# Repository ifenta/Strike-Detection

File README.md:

# Strike-Detection
Ideally I want to be able to:
- correct different strike and block techniques
- calculate speed of the strikes
- count how many times you do different strikes (flow hitting on a heavy bag for example)

With the camera, I want: 
- correct form now that I can see the whole body and depth
- detect if you are doing a lead or rear punch/kick
- see if I can improve transitions from different techniques

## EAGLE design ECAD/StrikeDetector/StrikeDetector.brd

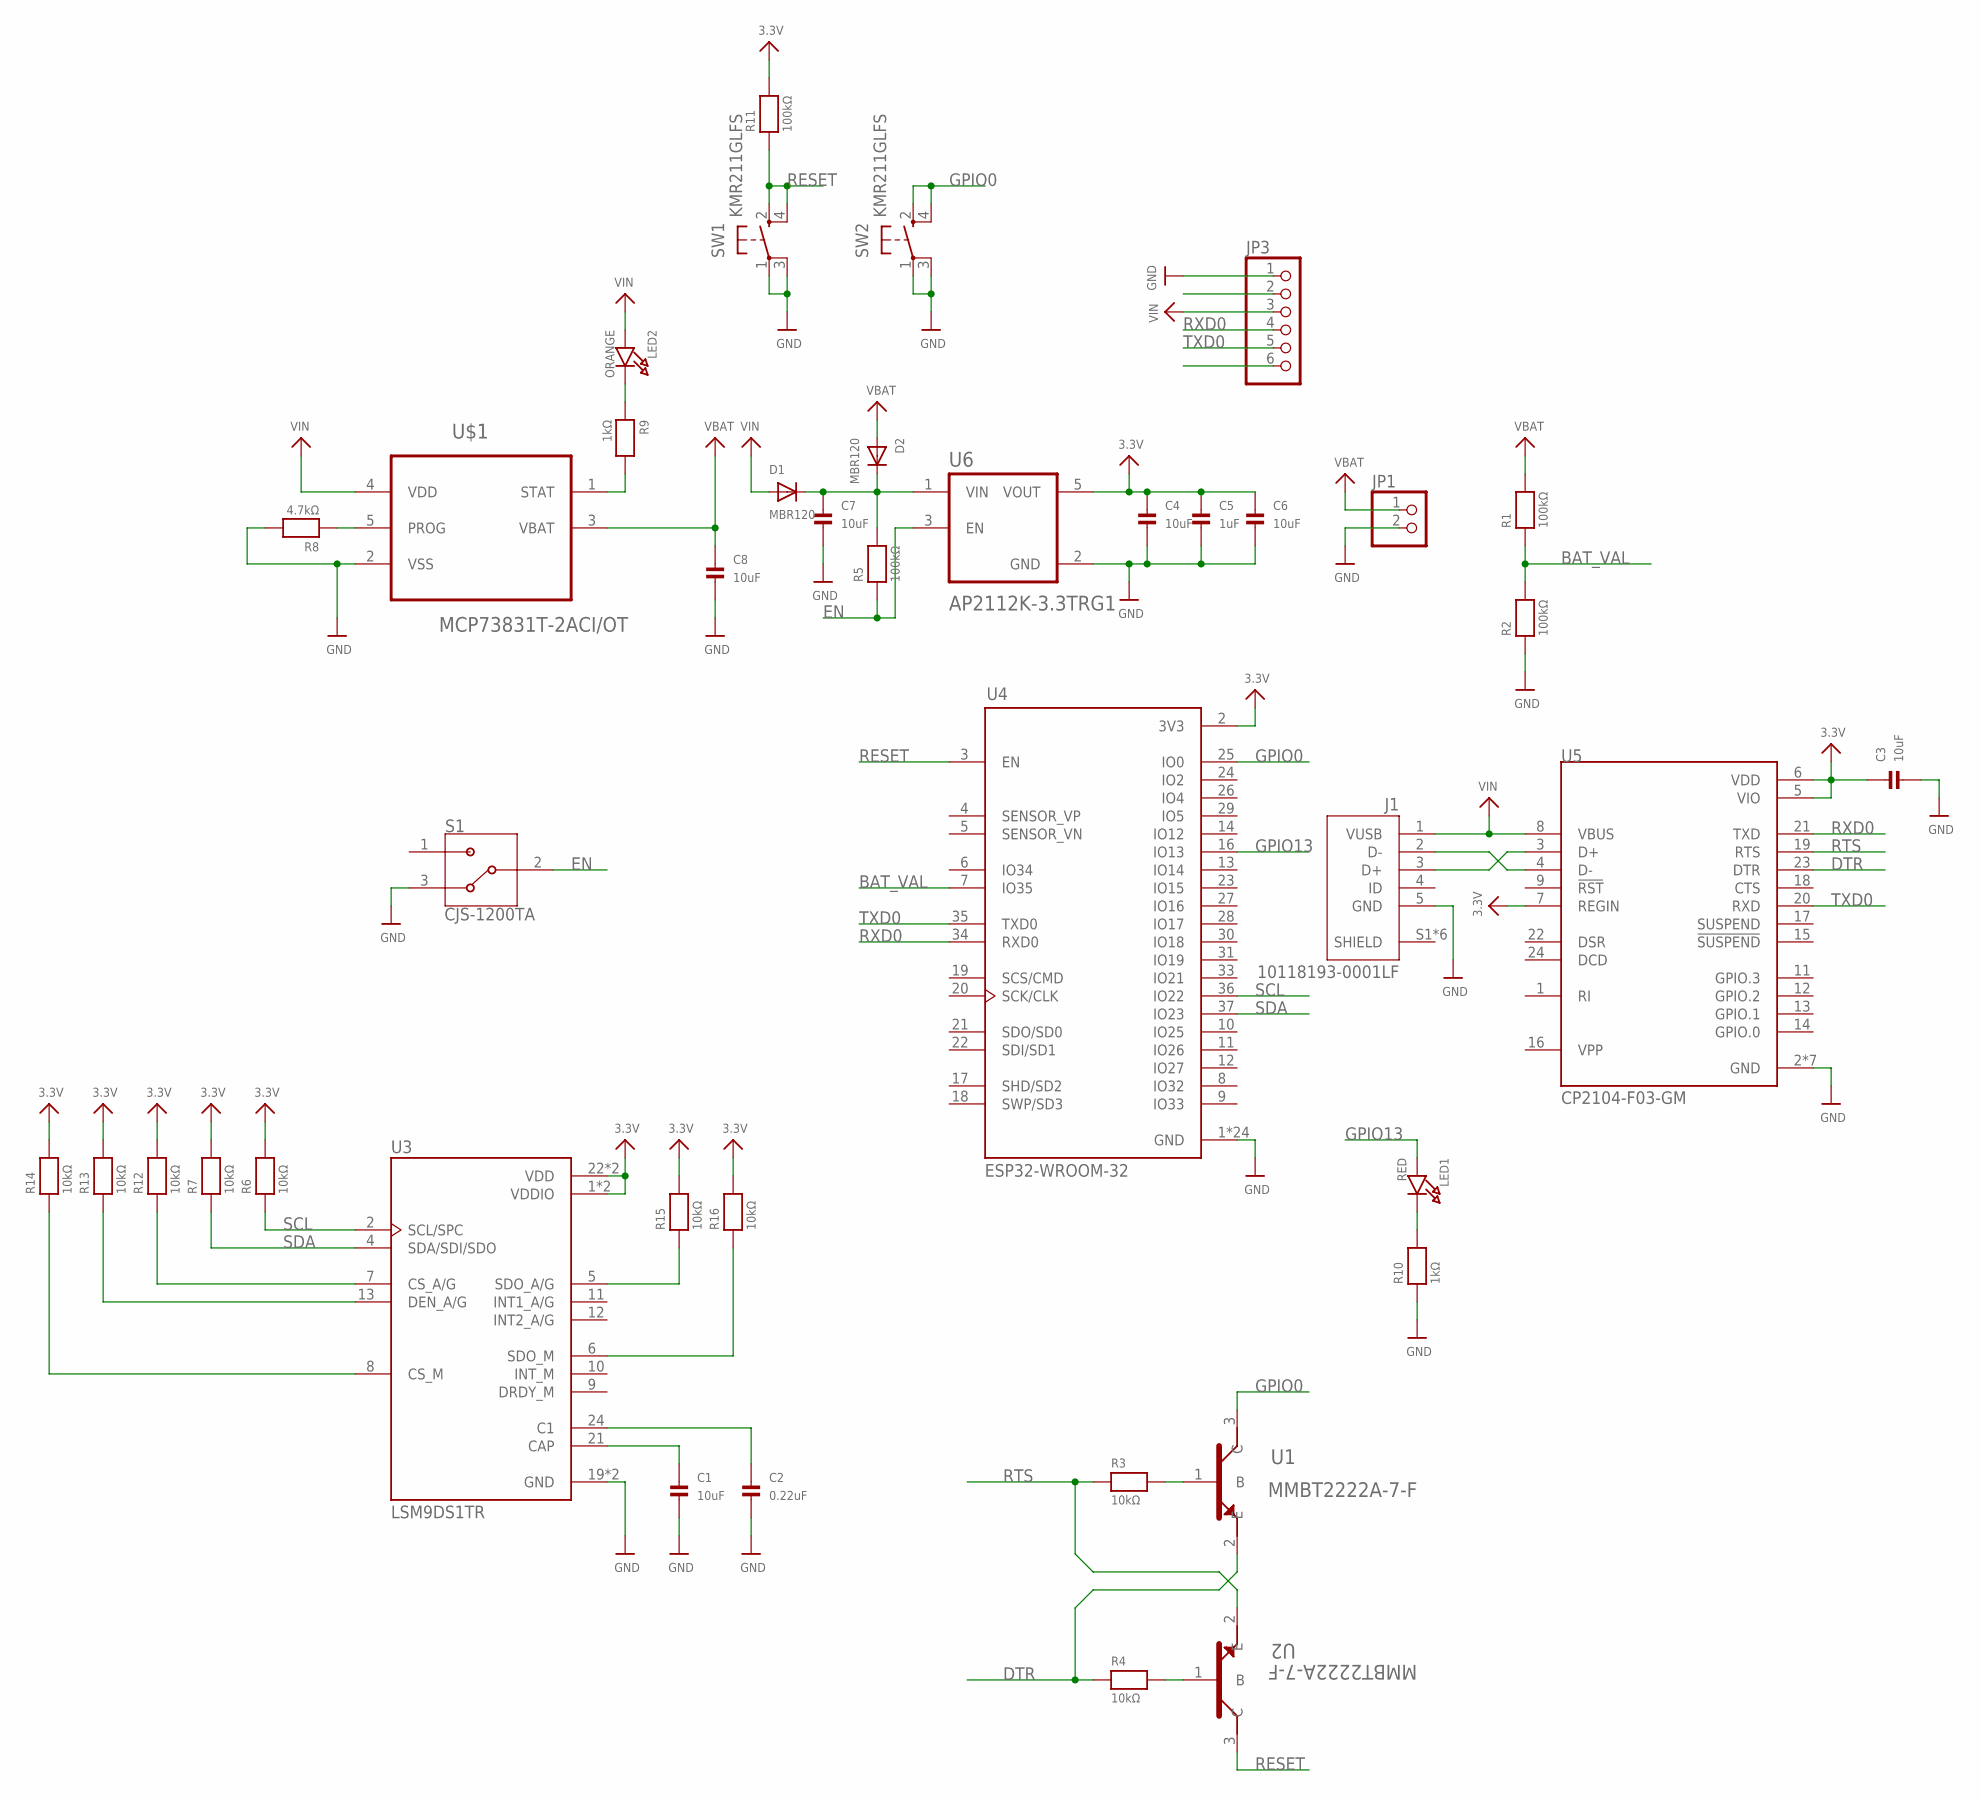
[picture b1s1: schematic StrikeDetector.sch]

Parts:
C1, C3, C4, C6, C7, C8: 10uF; 0603
C2: 0.22uF; 0603
C5: 1uF; 0603
D1, D2: MBR120; SOD-123
J1: 10118193-0001LF; FCI_10118193-0001LF
JP1: HEADER-1X2ROUND; 1X02_ROUND
JP3: HEADER-1X6ROUND; 1X06_ROUND
LED1: RED; CHIPLED_0603
LED2: ORANGE; CHIPLED_0603
R1, R2, R5, R11: 100kΩ; 0603
R3, R4, R6, R7, R12, R13, R14, R15, R16: 10kΩ; 0603
R8: 4.7kΩ; 0603
R9, R10: 1kΩ; 0603
S1: CJS-1200TA; SW_CJS-1200TA
SW1, SW2: KMR211GLFS; KMR2
U1, U2: MMBT2222A-7-F; SOT103P240X110-3N
U3: LSM9DS1TR; PQFN43P300X350X102-24N
U4: ESP32-WROOM-32; MODULE_ESP32-WROOM-32
U5: CP2104-F03-GM; QFN50P400X400X80-25N
U6: AP2112K-3.3TRG1; SOT95P285X140-5N
U$1: MCP73831T-2ACI/OT; SOT95P280X145-5N

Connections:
3.3V: C3.1, C4.1, C5.1, C6.1, R6.2, R7.2, R11.2, R12.2, R13.2, R14.2, R15.2, R16.2, U3.1 (VDDIO), U3.3 (VDDIO), U3.22 (VDD), U3.23 (VDD), U4.2 (3V3), U5.5 (VIO), U5.6 (VDD), U5.7 (REGIN), U6.5 (VOUT)
BAT_VAL: R1.1, R2.2, U4.7 (IO35)
DTR: R4.1, U1.2 (E), U5.23 (DTR)
EN: R5.1, S1.2, U6.3 (EN)
GND: C1.2, C2.2, C3.2, C4.2, C5.2, C6.2, C7.2, C8.2, J1.5 (GND), JP1.2, JP3.1, R2.1, R8.2, R10.1, S1.3, SW1.1, SW1.3 (P1), SW2.1, SW2.3 (P1), U3.19 (GND), U3.20 (GND), U4.1 (GND), U4.15 (GND), U4.38 (GND), U4.39_1 (GND), U4.39_2 (GND), U4.39_3 (GND), U4.39_4 (GND), U4.39_5 (GND), U4.39_6 (GND), U4.39_7 (GND), U4.39_8 (GND), U4.39_9 (GND), U4.39_10 (GND), U4.39_11 (GND), U4.39_12 (GND), U4.39_13 (GND), U4.39_14 (GND), U4.39_15 (GND), U4.39_16 (GND), U4.39_17 (GND), U4.39_18 (GND), U4.39_19 (GND), U4.39_20 (GND), U4.39_21 (GND), U5.2 (GND), U5.25 (GND), U5.THERM_1 (GND), U5.THERM_2 (GND), U5.THERM_3 (GND), U5.THERM_4 (GND), U5.THERM_5 (GND), U6.2 (GND), U$1.2 (VSS)
GPIO0: SW2.2 (S), SW2.4 (S1), U1.3 (C), U4.25 (IO0)
GPIO13: LED1.A, U4.16 (IO13)
unnamed: C1.1, U3.21 (CAP)
unnamed: J1.3 (D+), U5.3 (D+)
unnamed: J1.2 (D-), U5.4 (D-)
unnamed: C2.1, U3.24 (C1)
unnamed: R3.2, U1.1 (B)
unnamed: R4.2, U2.1 (B)
unnamed: C7.1, D1.C, D2.C, R5.2, U6.1 (VIN)
unnamed: R8.1, U$1.5 (PROG)
unnamed: R9.2, U$1.1 (STAT)
unnamed: LED2.C, R9.1
unnamed: LED1.C, R10.2
unnamed: R12.1, U3.7 (CS_A/G)
unnamed: R13.1, U3.13 (DEN_A/G)
unnamed: R14.1, U3.8 (CS_M)
unnamed: R15.1, U3.5 (SDO_A/G)
unnamed: R16.1, U3.6 (SDO_M)
RESET: R11.1, SW1.2 (S), SW1.4 (S1), U2.3 (C), U4.3 (EN)
RTS: R3.1, U2.2 (E), U5.19 (RTS)
RXD0: JP3.4, U4.34 (RXD0), U5.21 (TXD)
SCL: R6.1, U3.2 (SCL/SPC), U4.36 (IO22)
SDA: R7.1, U3.4 (SDA/SDI/SDO), U4.37 (IO23)
TXD0: JP3.5, U4.35 (TXD0), U5.20 (RXD)
VBAT: C8.1, D2.A, JP1.1, R1.2, U$1.3 (VBAT)
VIN: D1.A, J1.1 (VUSB), JP3.3, LED2.A, U5.8 (VBUS), U$1.4 (VDD)

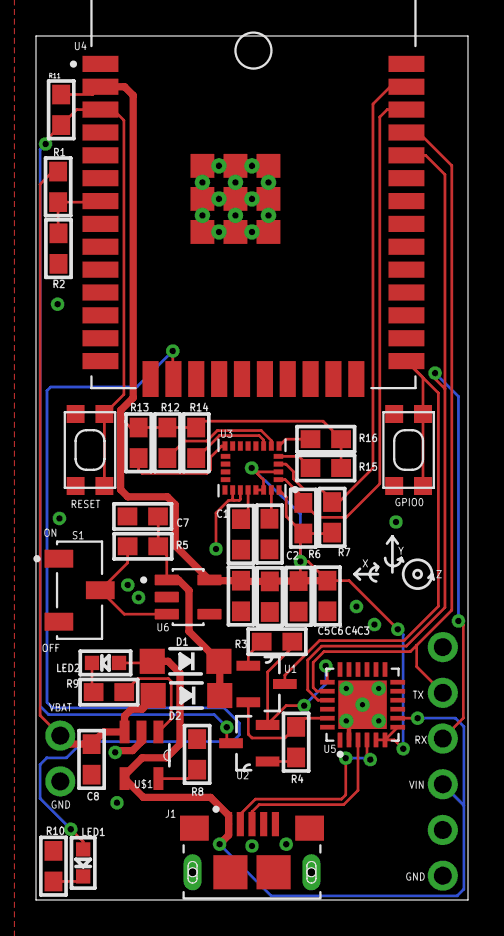
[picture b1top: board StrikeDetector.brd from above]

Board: 2 copper layers, 24.0 x 48.0 mm, 41 parts (0 on the bottom side), 31 nets.

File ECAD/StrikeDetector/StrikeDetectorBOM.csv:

"Qty";"Value";"Device";"Package";"Parts";"Description";"";
"1";"";"CP2104-F03-GM";"QFN50P400X400X80-25N";"U5";"USB-to-UART 1-CH 576byte FIFO 3.3V 24-Pin QFN EP T/R";"";
"1";"";"HEADER-1X2ROUND";"1X02_ROUND";"JP1";"PIN HEADER";"";
"1";"";"HEADER-1X6ROUND";"1X06_ROUND";"JP3";"PIN HEADER";"";
"1";"0.22uF";"CAP_CERAMIC0603";"0603";"C2";"Ceramic Capacitors";"";
"4";"100kΩ";"RESISTOR0603";"0603";"R1, R2, R5, R11";"Resistors";"";
"1";"10118193-0001LF";"10118193-0001LF";"FCI_10118193-0001LF";"J1";"Micro USB B Type Receptacle";"";
"2";"10kΩ";"RESISTOR0603";"0603";"R3, R4";"Resistors";"";
"6";"10uF";"CAP_CERAMIC0603";"0603";"C1, C3, C4, C6, C7, C8";"Ceramic Capacitors";"";
"2";"1kΩ";"RESISTOR0603";"0603";"R9, R10";"Resistors";"";
"1";"1uF";"CAP_CERAMIC0603";"0603";"C5";"Ceramic Capacitors";"";
"3";"4.7kΩ";"RESISTOR0603";"0603";"R6, R7, R8";"Resistors";"";
"1";"AP2112K-3.3TRG1";"AP2112K-3.3TRG1";"SOT95P285X140-5N";"U6";"AP2112 Series 0.6 A 3.3 V Fixed Output SMT LDO Linear Regulator - SOT23-5";"";
"1";"CJS-1200TA";"CJS-1200TA";"SW_CJS-1200TA";"S1";"Switch Slide N.O./N.C. SPDT Raised Slide 0.1A 24VDC J-Hook SMD Embossed T/R";"";
"1";"ESP32-WROOM-32";"ESP32-WROOM-32";"MODULE_ESP32-WROOM-32";"U4";"Bluetooth, WiFi Transceiver Module 2.4GHz ~ 2.5GHz Surface Mount";"";
"2";"KMR211GLFS";"SPST_TACT-KMR2";"KMR2";"SW1, SW2";"SMT 6mm switch, EVQQ2 series";"";
"1";"LSM9DS1TR";"LSM9DS1TR";"PQFN43P300X350X102-24N";"U3";"The LSM9DS1 is a system-in-package featuring a";"";
"2";"MBR120";"DIODESOD-123";"SOD-123";"D1, D2";"Diode";"";
"1";"MCP73831T-2ACI/OT";"MCP73831T-2ACI/OT";"SOT95P280X145-5N";"U$1";"Charge Management Controller";"";
"2";"MMBT2222A-7-F";"MMBT2222A-7-F";"SOT103P240X110-3N";"U1, U2";"NPN SMALL SIGNAL SURFACE MOUNT TRANSISTOR";"";
"1";"ORANGE";"LED0603";"CHIPLED_0603";"LED2";"LED";"";
"1";"RED";"LED0603";"CHIPLED_0603";"LED1";"LED";"";

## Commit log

2019-07-26 init commit
2020-02-17 Organizing
    Tranfering Arduino code to PlatformIO
    Organizing folders
2020-02-17 Clean up .ino file
2020-02-18 Sending Data Over Wifi
    Did a bit of organizing of files
    Able to send IMU data over UDP to my computer and run the python script to determine what kind of punch it is. Need to work a bit more on the analysis and how to incorporate it together with the rest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
2020-02-26 Created src
    Combine colletion of data over udp, read data, find the different strikes and plot data in one script. All in src folder
2020-02-26 Adding comments
2020-06-26 Completed Visualizing incoming UDP Data
2020-07-11 Working Live Algorithm
    - Data is updated live and algorithm works okay
    - Need to attach device to arm, and update code to read the correct directions
2020-07-11 Working Strike Detection
    Added check on gyroY to check twist to make it more accurate
2020-07-11 Auto reconnect
    - Added auto reconnect on the esp32 if it gets disconnected
    - send ack to esp32 every 3 sec
2020-07-14 Tested TCP Server
    - Tested TCP server and it was too slow to keep up with the live data
    - Organized the code a bit
2020-07-16 Tried TCP and everything broke
2020-07-16 Revert back to working days
2020-07-16 I dont know why, but its working tho!
2020-07-16 Revert "Revert back to working days"
    This reverts commit a13b234cb50495ef2fe12cd30969025bcb449abe.
2020-07-16 Beginning to make 4 threads for the different connections
2020-07-25 Working multi connect udp
    created seperate classes for readabilty and useablity
2020-08-12 Created ECAD schematic
2020-08-19 Finished Preliminary PCB Design
2020-08-19 Added dimension
2020-08-20 Updated PCB Design
2020-08-21 Updated board files
2020-09-03 Updated ECAD
    Added Pull up resistors for the pins I was missing
2020-09-25 Updating ecad stuff
2021-03-25 Update
    Added modification to save data to be processed in tensorflow

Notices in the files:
parts and their libraries:
microbuilder: This work is placed in the public domain, and may be freely used for commercial and non-commercial work with the following conditions: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
